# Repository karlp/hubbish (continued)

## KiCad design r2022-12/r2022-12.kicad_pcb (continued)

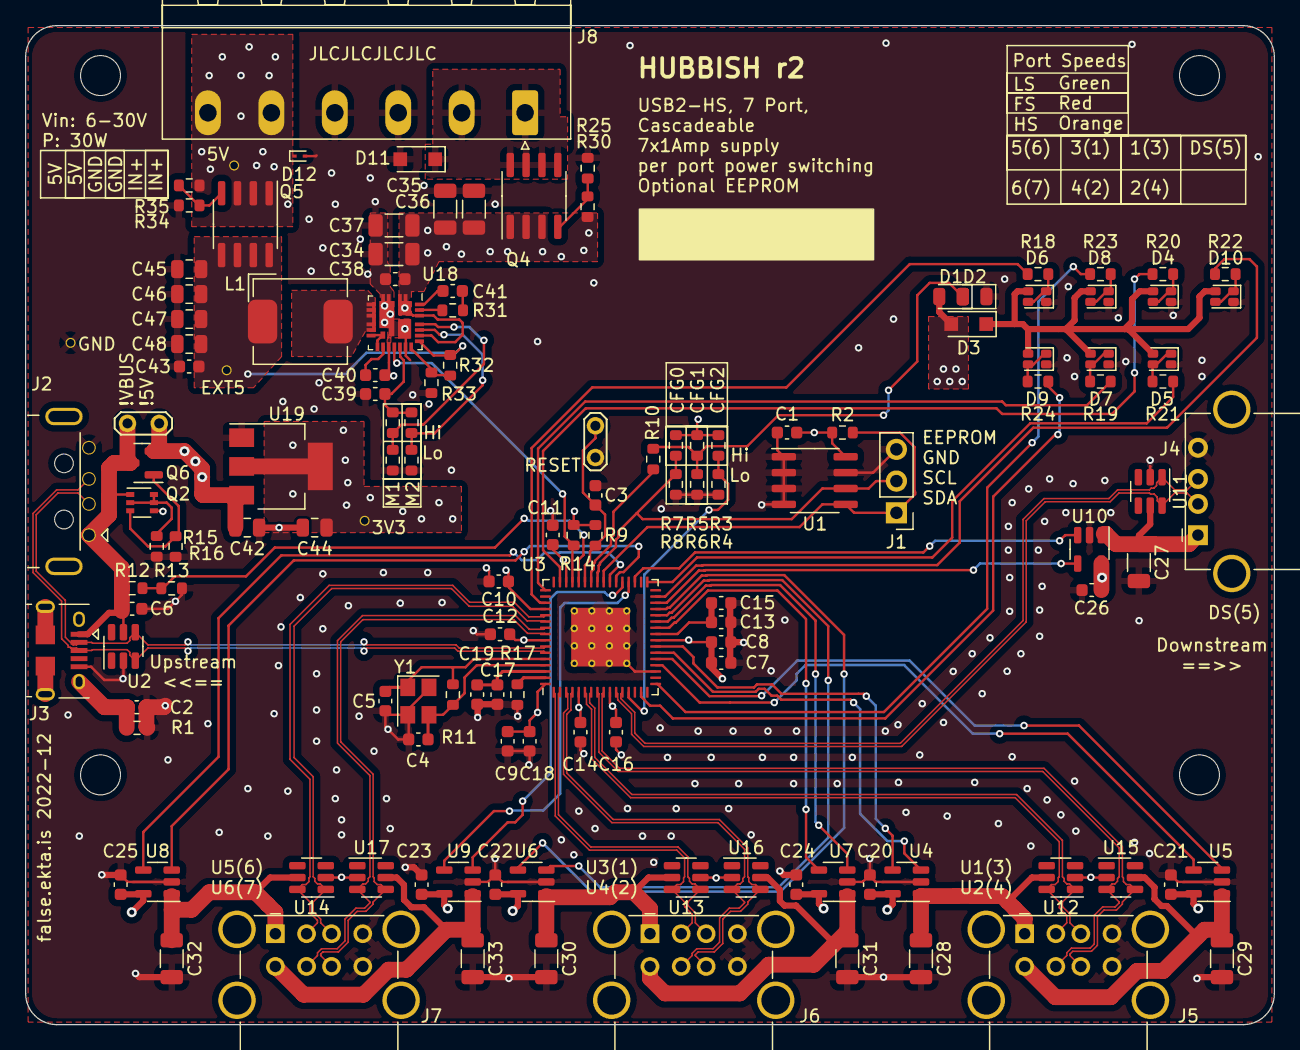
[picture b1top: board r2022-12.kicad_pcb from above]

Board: 4 copper layers, 100.0 x 80.0 mm, 138 parts (0 on the bottom side), 86 nets.

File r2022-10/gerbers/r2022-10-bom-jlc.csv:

"Comment","Designator","Footprint","JLCPCB Part #"
"100nF","C1,C2,C3,C8,C10,C11,C12,C14,C15,C16,C18,C19,C41,C44","Capacitor_SMD:C_0603_1608Metric","C14663"
"33pF","C4,C5","Capacitor_SMD:C_0603_1608Metric","C1663"
"1uF","C6,C7,C9,C13,C17,C20,C21,C22,C23,C24,C25,C26,C39,C40","Capacitor_SMD:C_0603_1608Metric","C15849"
"100uF","C27,C28,C29,C30,C31,C32,C33","Capacitor_SMD:C_1206_3216Metric","C15008"
"10uF/30+","C34,C35,C36,C37","Capacitor_SMD:C_1206_3216Metric","C13585 "
"100nF/30+","C38","Capacitor_SMD:C_0603_1608Metric","C14663"
"10uF","C42,C43,C45,C46,C47,C48","Capacitor_SMD:C_0805_2012Metric","C15850"
"HS1B","D1,D13","LED_SMD:LED_0805_2012Metric","C84256"
"HS1B","","LED_SMD:LED_0805_2012Metric","C84256"
"SM400x","D3","Diode_SMD:D_SOD-123F","C64898"
"LTST-C195KGJRKT","D4,D5,D6,D7,D8,D9,D10","LED_Dual:T1615_LiteOn_LTST_C195x","C125104"
"LTST-C195KGJRKT","","LED_Dual:T1615_LiteOn_LTST_C195x","C125104"
"LTST-C195KGJRKT","","LED_Dual:T1615_LiteOn_LTST_C195x","C125104"
"LTST-C195KGJRKT","","LED_Dual:T1615_LiteOn_LTST_C195x","C125104"
"LTST-C195KGJRKT","","LED_Dual:T1615_LiteOn_LTST_C195x","C125104"
"LTST-C195KGJRKT","","LED_Dual:T1615_LiteOn_LTST_C195x","C125104"
"USB_B_Micro (up)","J3","Connector_USB:USB_Micro-B_Amphenol_10118194-0001LF_Horizontal","C319164"
"USB_B_Micro (up)","","Connector_USB:USB_Micro-B_Amphenol_10118194-0001LF_Horizontal","C319164"
"USB_B_Micro (up)","","Connector_USB:USB_Micro-B_Amphenol_10118194-0001LF_Horizontal","C319164"
"USB_B_Micro (up)","","Connector_USB:USB_Micro-B_Amphenol_10118194-0001LF_Horizontal","C319164"
"USB_B_Micro (up)","","Connector_USB:USB_Micro-B_Amphenol_10118194-0001LF_Horizontal","C319164"
"1.5uH","L1","Inductor_SMD:L_Chilisin_BMRx00060630","C329386"
"HSM6115","Q1","Package_SO:SOIC-8_3.9x4.9mm_P1.27mm","C700986"
"S8550","Q2,Q4","Package_TO_SOT_SMD:SOT-23","C105432"
"AO3401A","Q3","Package_TO_SOT_SMD:SOT-23","C15127"
"330","R1,R10,R18,R19,R20,R21,R22,R30,R32,R33","Resistor_SMD:R_0603_1608Metric","C23138"
"10k","R2,R4,R5,R7,R11,R15,R16,R23,R34","Resistor_SMD:R_0603_1608Metric","C25804"
"100k","R9,R13,R14,R26","Resistor_SMD:R_0603_1608Metric","C25803"
"1M","R12","Resistor_SMD:R_0603_1608Metric","C22935"
"12k","R17","Resistor_SMD:R_0603_1608Metric","C22790"
"20k","R24","Resistor_SMD:R_0603_1608Metric","C4184"
"20k","","Resistor_SMD:R_0603_1608Metric","C4184"
"510k","R28","Resistor_SMD:R_0603_1608Metric","C23192"
"0","R29","Resistor_SMD:R_0603_1608Metric","C21189"
"75k","R31","Resistor_SMD:R_0603_1608Metric","C23242"
"75k","","Resistor_SMD:R_0603_1608Metric","C23242"
"2k i2c eeprom","U1","Package_SO:SOIC-8_3.9x4.9mm_P1.27mm","C7562"
"NUP4202","U2,U11,U12,U13,U14,U15,U16,U17","Package_TO_SOT_SMD:SOT-23-6","C85364"
"USB2517","U3","Package_DFN_QFN:QFN-64-1EP_9x9mm_P0.5mm_EP4.7x4.7mm_ThermalVias","C626667"
"APL3511C","U4,U5,U6,U7,U8,U9,U10","Package_TO_SOT_SMD:SOT-23-5","C211404"
"SiC437AED","U18","Package_DFN_QFN:Vishay_MLP-44L_4x4","C2071432"
"AMS1117-33","U19","Package_TO_SOT_SMD:SOT-223-3_TabPin2","C6186"
"24MHz","Y1","Crystal:Crystal_SMD_3225-4Pin_3.2x2.5mm","C70590"

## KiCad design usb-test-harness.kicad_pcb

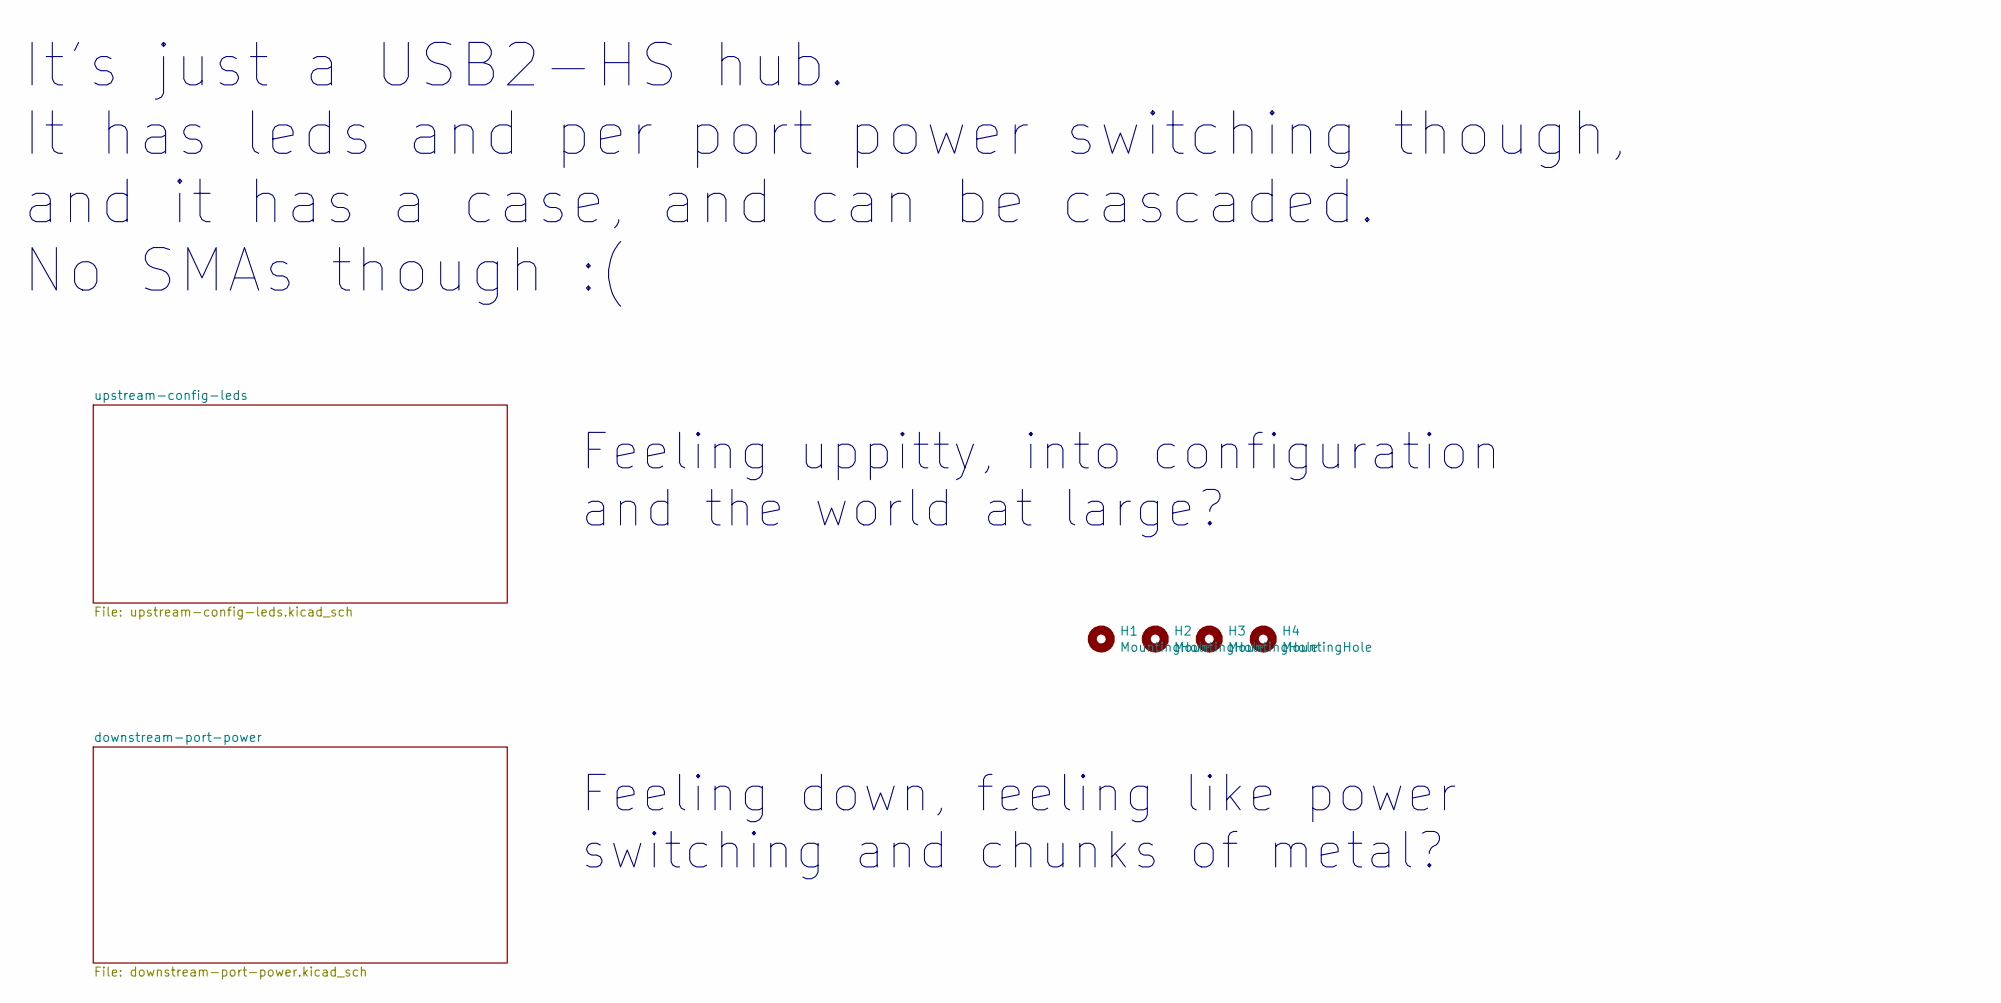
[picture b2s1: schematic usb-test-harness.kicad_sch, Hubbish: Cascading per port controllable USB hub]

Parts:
H1, H2, H3, H4: MountingHole; MountingHole_2.7mm_M2.5

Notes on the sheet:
It's just a USB2-HS hub. It has leds and per port power switching though, and it has a case, and can be cascaded. No SMAs though :(
Feeling uppitty, into configuration and the world at large?
Feeling down, feeling like power switching and chunks of metal?

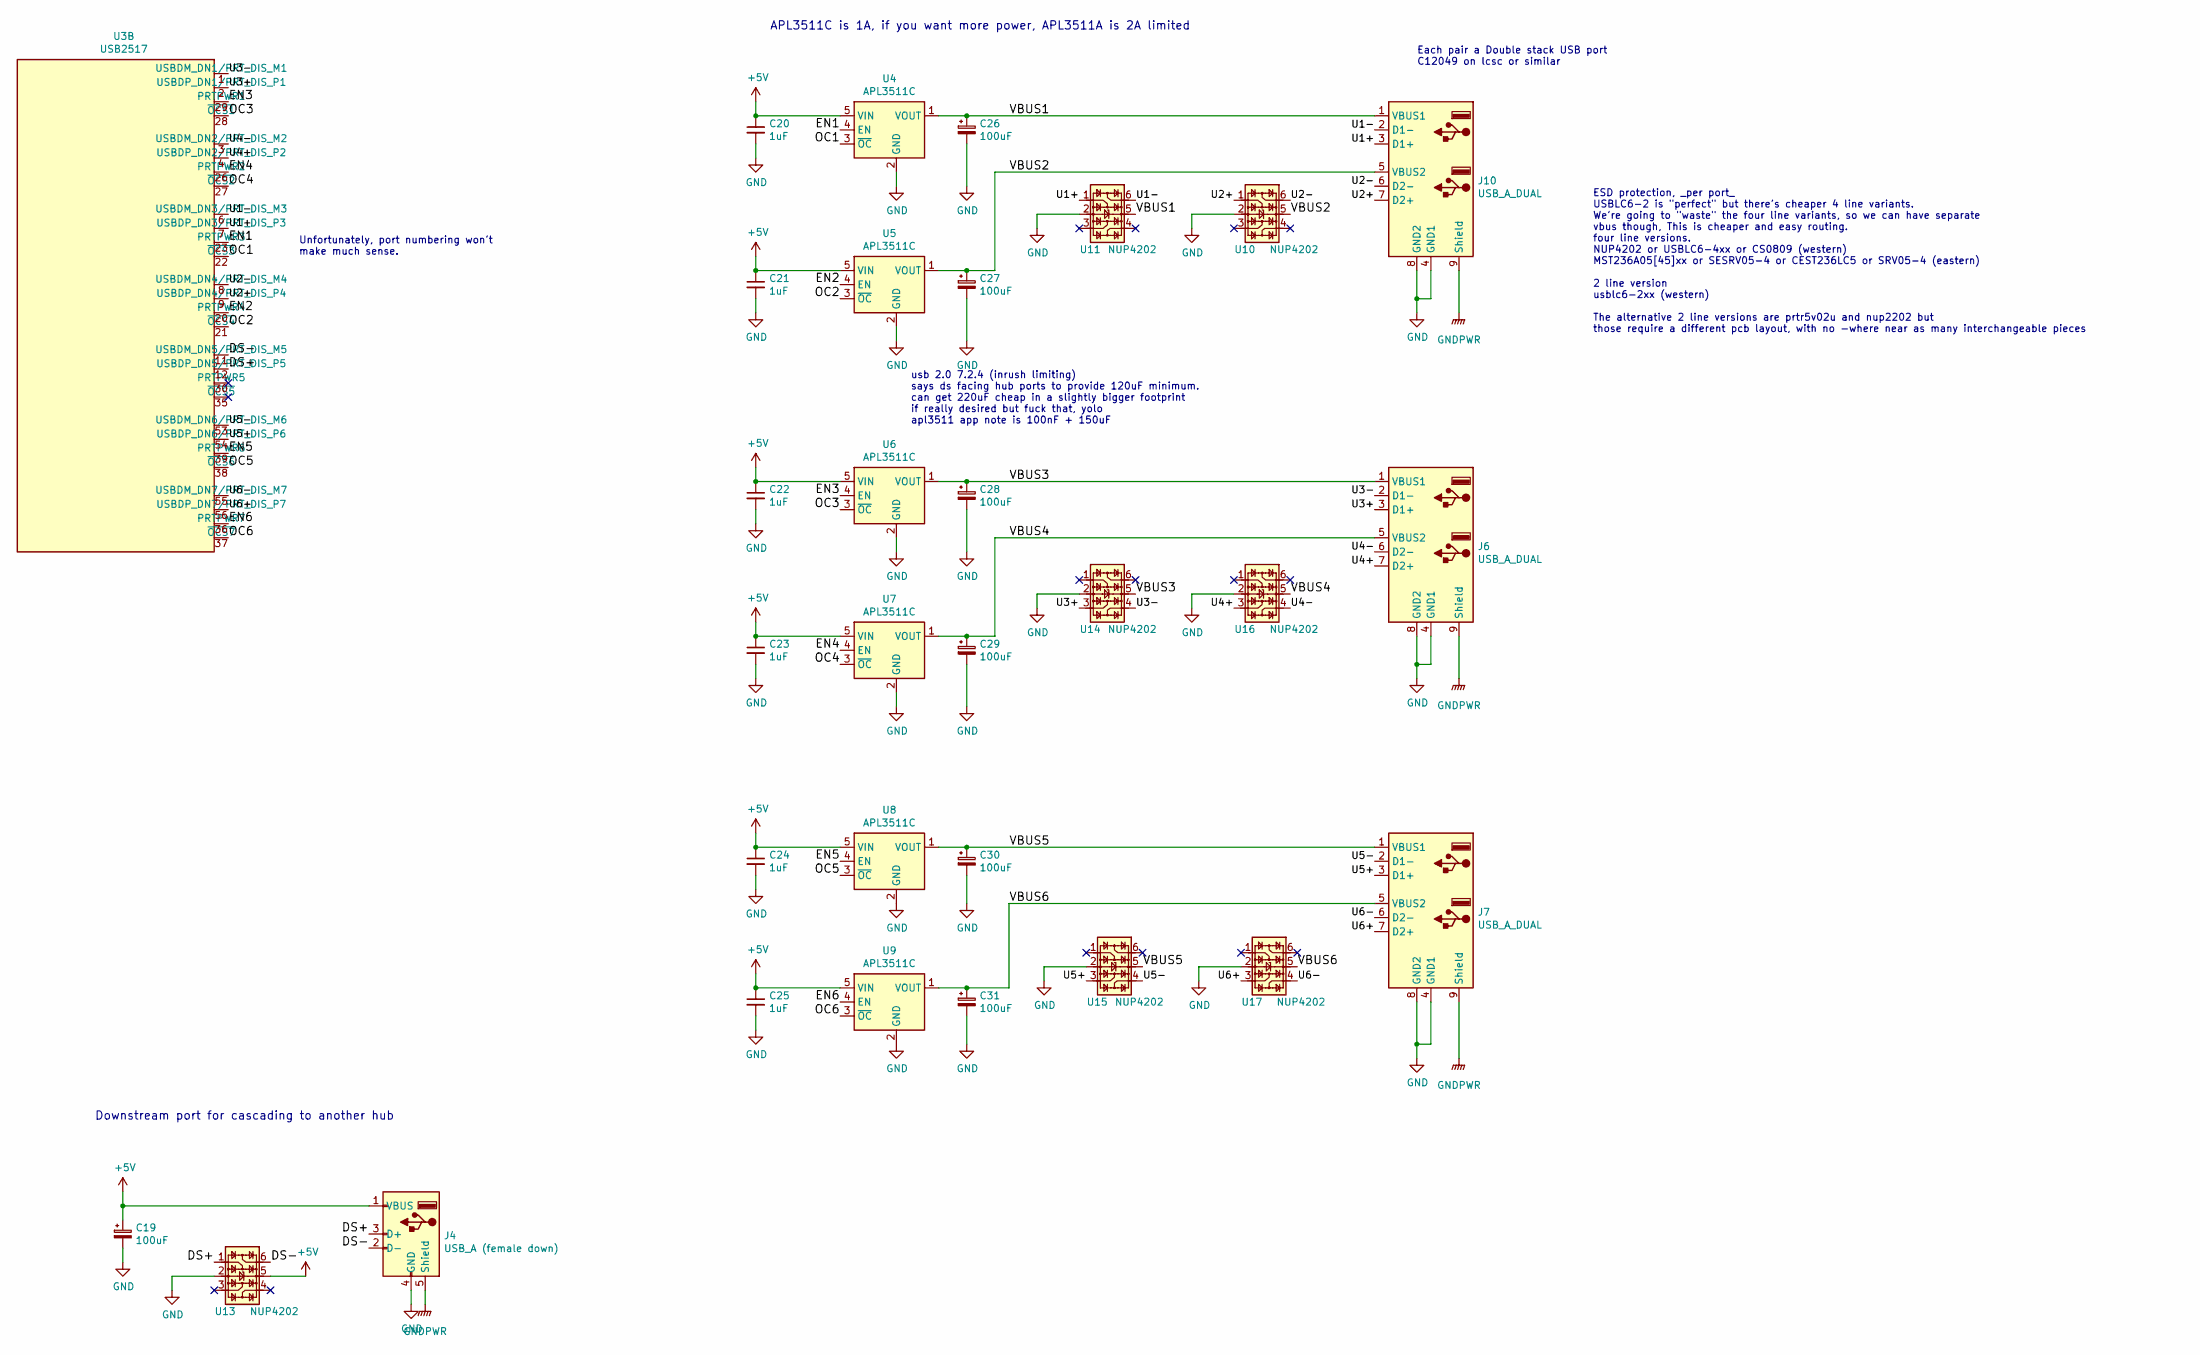
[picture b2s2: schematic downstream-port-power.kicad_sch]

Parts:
C19, C26, C27, C28, C29, C30, C31: 100uF; CP_Elec_5x5.4
C20, C21, C22, C23, C24, C25: 1uF; C_0603_1608Metric
J4: USB_A (female down); USB_A_Stewart_SS-52100-001_Horizontal; MPN C42643 or SS-52100 compatible
J6, J7, J10: USB_A_DUAL; USB_A_Wuerth_61400826021_Horizontal_Stacked
U3: USB2517; QFN-64-1EP_9x9mm_P0.5mm_EP4.7x4.7mm_ThermalVias
U4, U5, U6, U7, U8, U9: APL3511C; SOT-23-5
U10, U11, U13, U14, U15, U16, U17: NUP4202; SOT-23-6

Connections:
+5V: C19.1, C20.1, C21.1, C22.1, C23.1, C24.1, C25.1, J4.1 (VBUS), U4.5 (VIN), U5.5 (VIN), U6.5 (VIN), U7.5 (VIN), U8.5 (VIN), U9.5 (VIN), U13.5; also elsewhere on the board
/downstream-port-power/DS+: J4.3 (D+), U3.12 (USBDP_DN5/PRT_DIS_P5), U13.1
/downstream-port-power/DS-: J4.2 (D-), U3.11 (USBDM_DN5/PRT_DIS_M5), U13.6
/downstream-port-power/EN1: U3.23 (PRTPWR3), U4.4 (EN)
/downstream-port-power/EN2: U3.20 (PRTPWR4), U5.4 (EN)
/downstream-port-power/EN3: U3.29 (PRTPWR1), U6.4 (EN)
/downstream-port-power/EN4: U3.26 (PRTPWR2), U7.4 (EN)
/downstream-port-power/EN5: U3.39 (PRTPWR6), U8.4 (EN)
/downstream-port-power/EN6: U3.36 (PRTPWR7), U9.4 (EN)
/downstream-port-power/OC1: U3.22 (~OCS3), U4.3 (~OC)
/downstream-port-power/OC2: U3.21 (~OCS4), U5.3 (~OC)
/downstream-port-power/OC3: U3.28 (~OCS1), U6.3 (~OC)
/downstream-port-power/OC4: U3.27 (~OCS2), U7.3 (~OC)
/downstream-port-power/OC5: U3.38 (~OCS6), U8.3 (~OC)
/downstream-port-power/OC6: U3.37 (~OCS7), U9.3 (~OC)
/downstream-port-power/U1+: J10.3 (D1+), U3.7 (USBDP_DN3/PRT_DIS_P3), U11.1
/downstream-port-power/U1-: J10.2 (D1-), U3.6 (USBDM_DN3/PRT_DIS_M3), U11.6
/downstream-port-power/U2+: J10.7 (D2+), U3.9 (USBDP_DN4/PRT_DIS_P4), U10.1
/downstream-port-power/U2-: J10.6 (D2-), U3.8 (USBDM_DN4/PRT_DIS_M4), U10.6
/downstream-port-power/U3+: J6.3 (D1+), U3.2 (USBDP_DN1/PRT_DIS_P1), U14.3
/downstream-port-power/U3-: J6.2 (D1-), U3.1 (USBDM_DN1/PRT_DIS_M1), U14.4
/downstream-port-power/U4+: J6.7 (D2+), U3.4 (USBDP_DN2/PRT_DIS_P2), U16.3
/downstream-port-power/U4-: J6.6 (D2-), U3.3 (USBDM_DN2/PRT_DIS_M2), U16.4
/downstream-port-power/U5+: J7.3 (D1+), U3.54 (USBDP_DN6/PRT_DIS_P6), U15.3
/downstream-port-power/U5-: J7.2 (D1-), U3.53 (USBDM_DN6/PRT_DIS_M6), U15.4
/downstream-port-power/U6+: J7.7 (D2+), U3.56 (USBDP_DN7/PRT_DIS_P7), U17.3
/downstream-port-power/U6-: J7.6 (D2-), U3.55 (USBDM_DN7/PRT_DIS_M7), U17.4
/downstream-port-power/VBUS1: C26.1, J10.1 (VBUS1), U4.1 (VOUT), U11.5
/downstream-port-power/VBUS2: C27.1, J10.5 (VBUS2), U5.1 (VOUT), U10.5
/downstream-port-power/VBUS3: C28.1, J6.1 (VBUS1), U6.1 (VOUT), U14.5
/downstream-port-power/VBUS4: C29.1, J6.5 (VBUS2), U7.1 (VOUT), U16.5
/downstream-port-power/VBUS5: C30.1, J7.1 (VBUS1), U8.1 (VOUT), U15.5
/downstream-port-power/VBUS6: C31.1, J7.5 (VBUS2), U9.1 (VOUT), U17.5
GND: C19.2, C20.2, C21.2, C22.2, C23.2, C24.2, C25.2, C26.2, C27.2, C28.2, C29.2, C30.2, C31.2, J4.4 (GND), J6.4 (GND1), J6.8 (GND2), J7.4 (GND1), J7.8 (GND2), J10.4 (GND1), J10.8 (GND2), U4.2 (GND), U5.2 (GND), U6.2 (GND), U7.2 (GND), U8.2 (GND), U9.2 (GND), U10.2, U11.2, U13.2, U14.2, U15.2, U16.2, U17.2; also elsewhere on the board
GNDPWR: J4.5 (Shield), J6.9 (Shield), J7.9 (Shield), J10.9 (Shield); also elsewhere on the board

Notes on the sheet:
Downstream port for cascading to another hub
Unfortunately, port numbering won't make much sense.
APL3511C is 1A, if you want more power, APL3511A is 2A limited
usb 2.0 7.2.4 (inrush limiting) says ds facing hub ports to provide 120uF minimum. can get 220uF cheap in a slightly bigger footprint if really desired but fuck that, yolo apl3511 app note is 100nF + 150uF
Each pair a Double stack USB port C12049 on lcsc or similar
ESD protection, _per port_ USBLC6-2 is "perfect" but there's cheaper 4 line variants. We're going to "waste" the four line variants, so we can have separate vbus though, This is cheaper and easy routing. four line versions. NUP4202 or USBLC6-4xx or CS0809 (western) MST236A05[45]xx or SESRV05-4 or C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

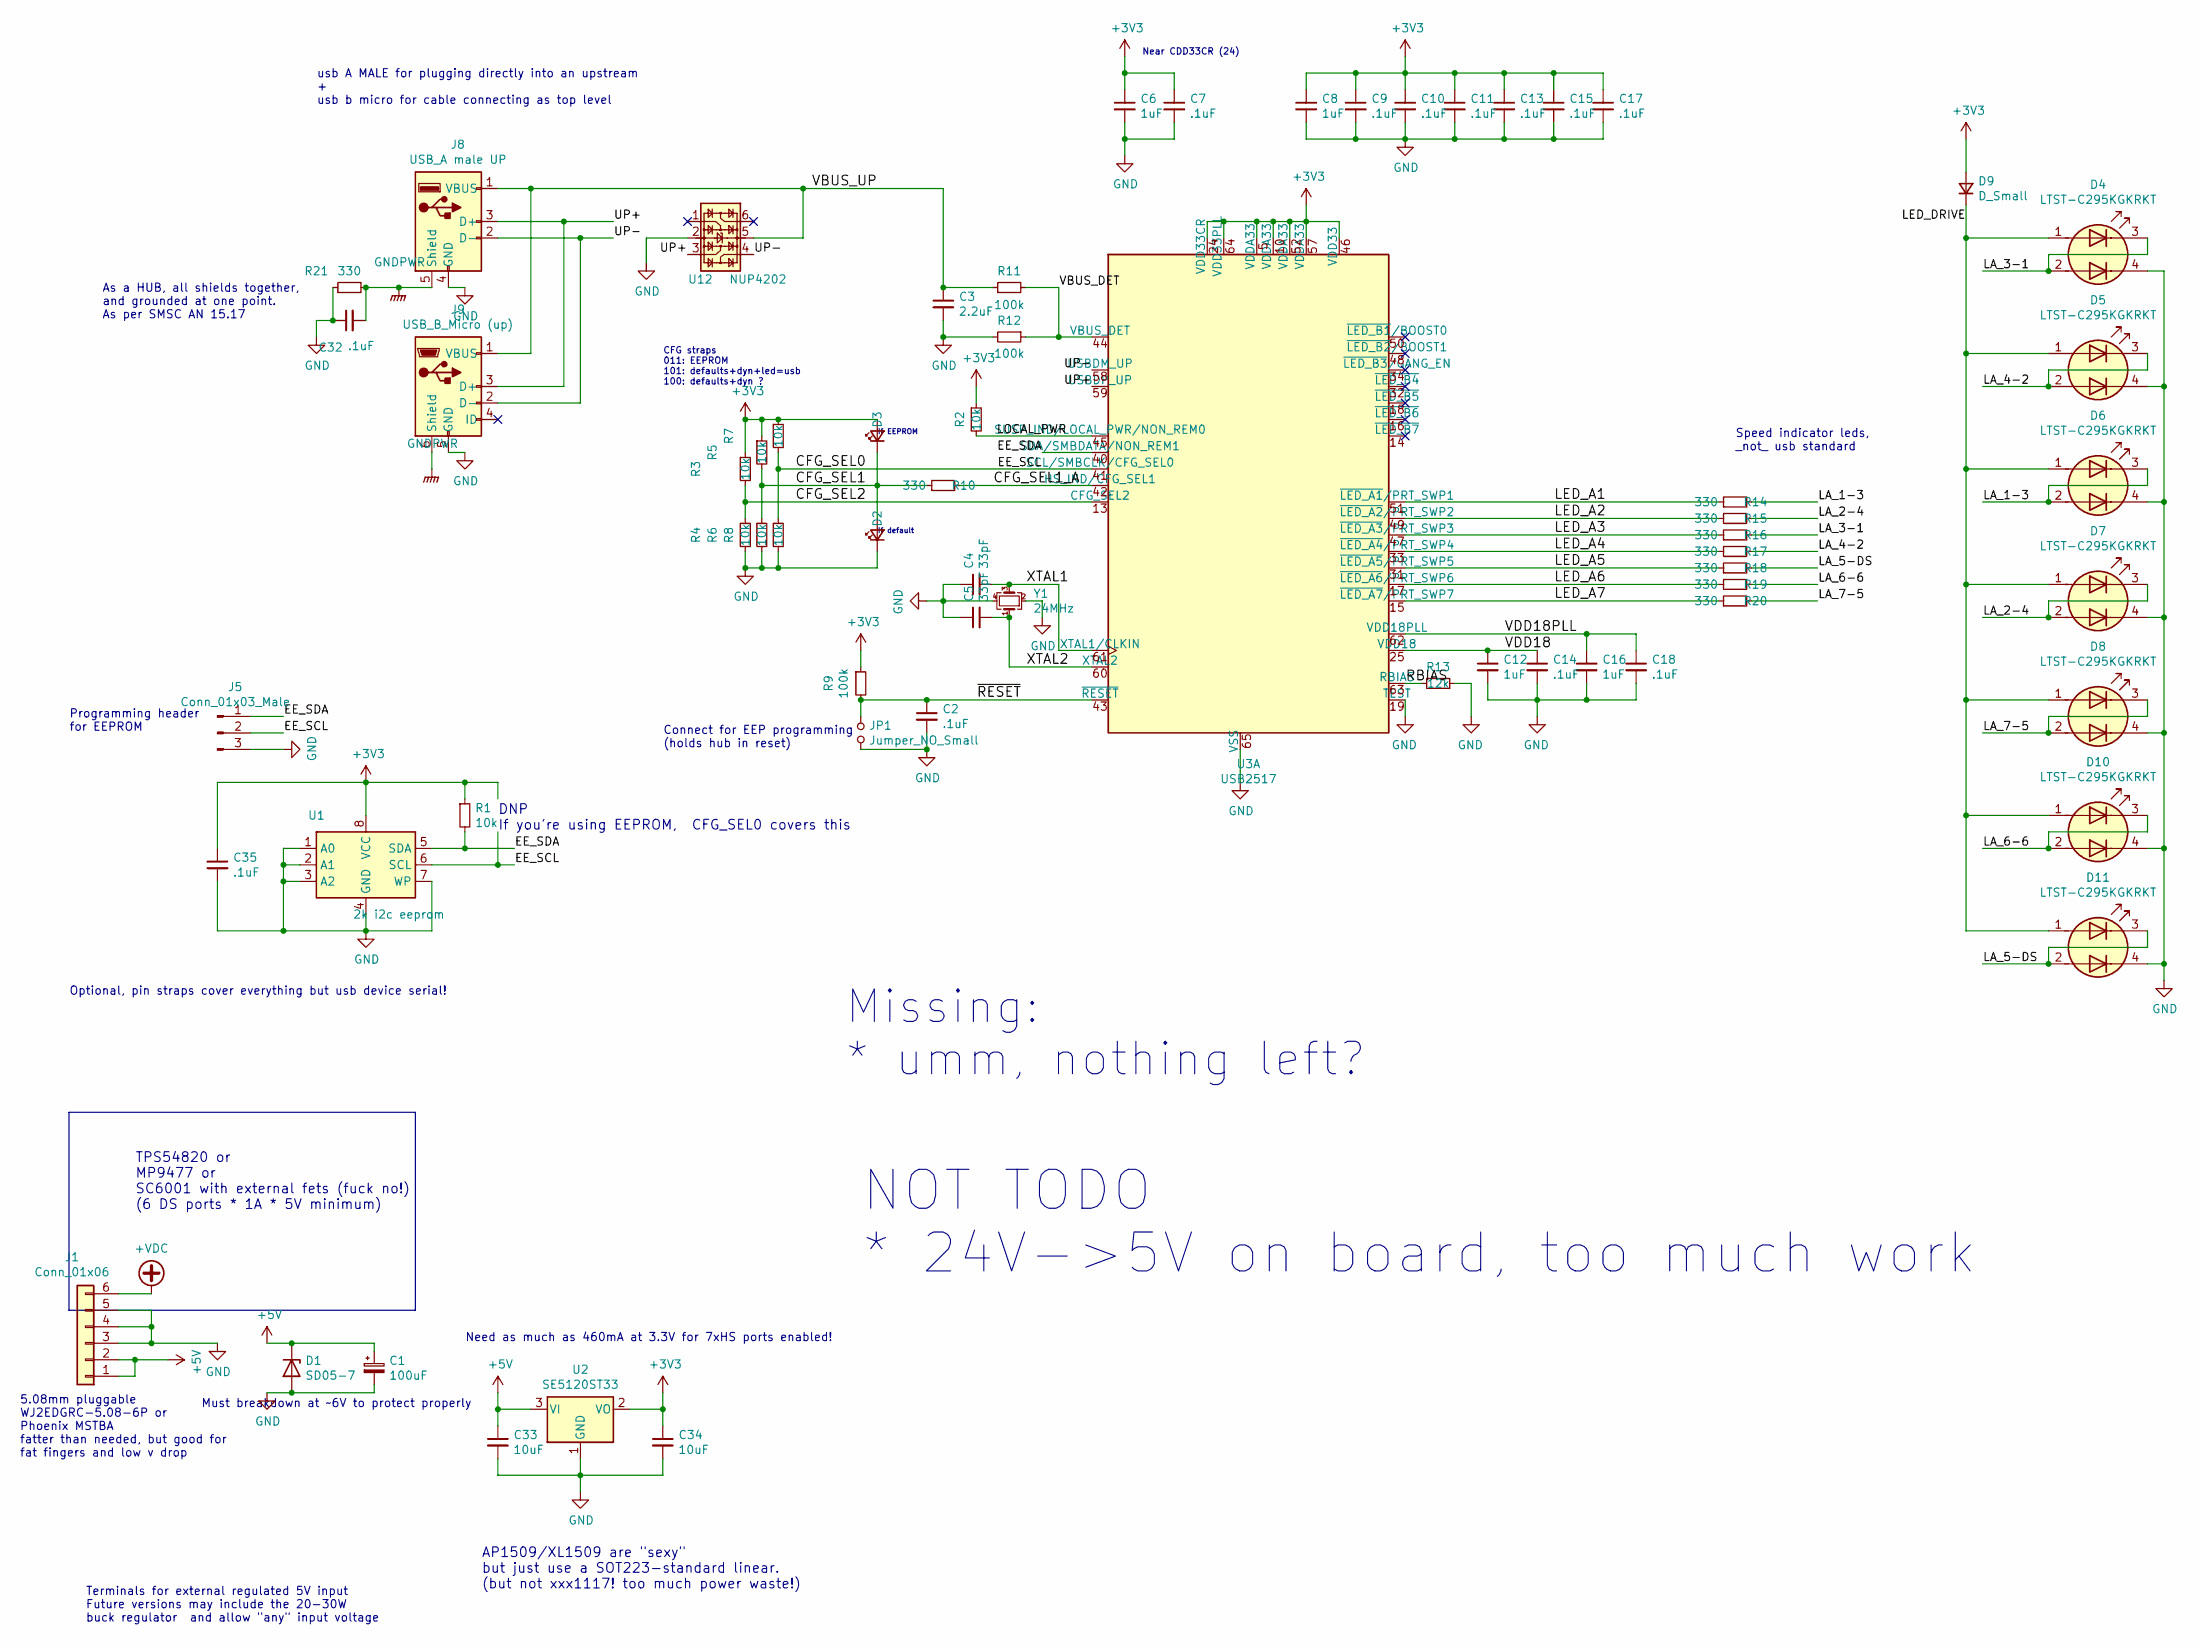
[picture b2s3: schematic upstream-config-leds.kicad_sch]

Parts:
C1: 100uF; CP_Elec_5x5.4
C2, C7, C9, C10, C11, C13, C14, C15, C17, C18, C32, C35: .1uF; C_0603_1608Metric
C3: 2.2uF; C_0603_1608Metric
C4, C5: 33pF; C_0603_1608Metric
C6, C8, C12, C16: 1uF; C_0603_1608Metric
C33, C34: 10uF; C_0603_1608Metric
D1: SD05-7; D_SOD-323
D2: HS1A; LED_0603_1608Metric
D3: HS1B; LED_0603_1608Metric
D4, D5, D6, D7, D8, D10, D11: LTST-C295KGKRKT; LED_LiteOn_LTST-C295K
D9: D_Small; D_SOD-323
J1: Conn_01x06; PhoenixContact_MSTBA_2,5_6-G-5,08_1x06_P5.08mm_Horizontal
J5: Conn_01x03_Male; PinHeader_1x03_P2.54mm_Vertical
J8: USB_A male UP; USB_A_Plug_SOFNG_USB-05; MPN SOFNG USB-05
J9: USB_B_Micro (up); USB_Micro-B_Amphenol_10118194-0001LF_Horizontal; MPN U254-051T-4BH23-S2B
JP1: Jumper_NO_Small; PinHeader_1x02_P2.54mm_Vertical
R1, R2, R3, R4, R5, R6, R7, R8: 10k; R_0603_1608Metric
R9, R11, R12: 100k; R_0603_1608Metric
R10, R14, R15, R16, R17, R18, R19, R20, R21: 330; R_0603_1608Metric
R13: 12k; R_0603_1608Metric
U1: 2k i2c eeprom; SOIC-8_3.9x4.9mm_P1.27mm; MPN FT24C02A
U2: SE5120ST33; SOT-223-3_TabPin2; MPN SE5120ST33
U3: USB2517; QFN-64-1EP_9x9mm_P0.5mm_EP4.7x4.7mm_ThermalVias
U12: NUP4202; SOT-363_SC-70-6
Y1: 24MHz; Crystal_SMD_3225-4Pin_3.2x2.5mm

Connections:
+3V3: C6.1, C7.1, C8.1, C9.1, C10.1, C11.1, C13.1, C15.1, C17.1, C34.1, C35.1, D3.2 (A), D9.2 (A), R1.1, R2.1, R3.1, R5.1, R7.1, R9.1, U1.8 (VCC), U2.2 (VO), U3.5 (VDDA33), U3.10 (VDDA33), U3.24 (VDD33CR), U3.46 (VDD33), U3.52 (VDDA33), U3.57 (VDDA33), U3.64 (VDD33PLL)
+5V: C1.1, C33.1, D1.1 (K), J1.1, J1.2, U2.3 (VI); also elsewhere on the board
/upstream-config-leds/CFG_SEL0: J5.2, R7.2, R8.1, U1.6 (SCL), U3.41 (SCL/SMBCLK/CFG_SEL0)
/upstream-config-leds/CFG_SEL1: D2.2 (A), D3.1 (K), R5.2, R6.1, R10.1
/upstream-config-leds/CFG_SEL1_A: R10.2, U3.42 (HS_IND/CFG_SEL1)
/upstream-config-leds/CFG_SEL2: R3.2, R4.1, U3.13 (CFG_SEL2)
/upstream-config-leds/EE_SDA: J5.1, R1.2, U1.5 (SDA), U3.40 (SDA/SMBDATA/NON_REM1)
/upstream-config-leds/LA_1-3: D6.2 (A2), D6.3 (K1), R14.2
/upstream-config-leds/LA_2-4: D7.2 (A2), D7.3 (K1), R15.2
/upstream-config-leds/LA_3-1: D4.2 (A2), D4.3 (K1), R16.2
/upstream-config-leds/LA_4-2: D5.2 (A2), D5.3 (K1), R17.2
/upstream-config-leds/LA_5-DS: D11.2 (A2), D11.3 (K1), R18.2
/upstream-config-leds/LA_6-6: D10.2 (A2), D10.3 (K1), R19.2
/upstream-config-leds/LA_7-5: D8.2 (A2), D8.3 (K1), R20.2
/upstream-config-leds/LED_A1: R14.1, U3.51 (~LED_A1~/PRT_SWP1)
/upstream-config-leds/LED_A2: R15.1, U3.49 (~LED_A2~/PRT_SWP2)
/upstream-config-leds/LED_A3: R16.1, U3.47 (~LED_A3~/PRT_SWP3)
/upstream-config-leds/LED_A4: R17.1, U3.33 (~LED_A4~/PRT_SWP4)
/upstream-config-leds/LED_A5: R18.1, U3.31 (~LED_A5~/PRT_SWP5)
/upstream-config-leds/LED_A6: R19.1, U3.17 (~LED_A6~/PRT_SWP6)
/upstream-config-leds/LED_A7: R20.1, U3.15 (~LED_A7~/PRT_SWP7)
/upstream-config-leds/LED_DRIVE: D4.1 (A1), D5.1 (A1), D6.1 (A1), D7.1 (A1), D8.1 (A1), D9.1 (K), D10.1 (A1), D11.1 (A1)
/upstream-config-leds/LOCAL_PWR: R2.2, U3.45 (SUSP_IND/LOCAL_PWR/NON_REM0)
/upstream-config-leds/RBIAS: R13.1, U3.63 (RBIAS)
/upstream-config-leds/UP+: J8.3 (D+), J9.3 (D+), U3.59 (USBDP_UP), U12.3
/upstream-config-leds/UP-: J8.2 (D-), J9.2 (D-), U3.58 (USBDM_UP), U12.4
/upstream-config-leds/VBUS_DET: R11.2, R12.1, U3.44 (VBUS_DET)
/upstream-config-leds/VBUS_UP: C3.1, J8.1 (VBUS), J9.1 (VBUS), R11.1, U12.5
/upstream-config-leds/VDD18: C12.1, C14.1, U3.25 (VDD18)
/upstream-config-leds/VDD18PLL: C16.1, C18.1, U3.62 (VDD18PLL)
/upstream-config-leds/XTAL1: C4.2, U3.61 (XTAL1/CLKIN), Y1.3
/upstream-config-leds/XTAL2: C5.2, U3.60 (XTAL2), Y1.1
/upstream-config-leds/~RESET: C2.1, JP1.1, R9.2, U3.43 (~RESET)
GND: C1.2, C2.2, C3.2, C4.1, C5.1, C6.2, C7.2, C8.2, C9.2, C10.2, C11.2, C12.2, C13.2, C14.2, C15.2, C16.2, C17.2, C18.2, C32.1, C33.2, C34.2, C35.2, D1.2 (A), D2.1 (K), D4.4 (K2), D5.4 (K2), D6.4 (K2), D7.4 (K2), D8.4 (K2), D10.4 (K2), D11.4 (K2), J1.3, J1.4, J1.5, J5.3, J8.4 (GND), J9.5 (GND), JP1.2, R4.2, R6.2, R8.2, R12.2, R13.2, R21.1, U1.1 (A0), U1.2 (A1), U1.3 (A2), U1.4 (GND), U1.7 (WP), U2.1 (GND), U3.19 (TEST), U3.65 (VSS), U12.2, Y1.2, Y1.4; also elsewhere on the board
GNDPWR: C32.2, J8.5 (Shield), J9.6 (Shield), R21.2; also elsewhere on the board

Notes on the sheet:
5.08mm pluggable WJ2EDGRC-5.08-6P or Phoenix MSTBA fatter than needed, but good for fat fingers and low v drop
Programming header for EEPROM
Optional, pin straps cover everything but usb device serial!
Terminals for external regulated 5V input Future versions may include the 20-30W buck regulator and allow "any" input voltage
As a HUB, all shields together, and grounded at one point. As per SMSC AN 15.17
TPS54820 or MP9477 or SC6001 with external fets (fuck no!) (6 DS ports * 1A * 5V minimum)
Must breakdown at ~~6V to protect properly
usb A MALE for plugging directly into an upstream + usb b micro for cable connecting as top level
Need as much as 460mA at 3.3V for 7xHS ports enabled!
AP1509/XL1509 are "sexy" but just use a SOT223-standard linear. (but not xxx1117! too much power waste!)
DNP If you're using EEPROM, CFG_SEL0 covers this
CFG straps 011: EEPROM 101: defaults+dyn+led=usb 100: defaults+dyn ?
Connect for EEP programming (holds hub in reset)
Missing: * umm, nothing left?
NOT TODO * 24V->5V on board, too much work
If EEPROM
If default
Near CDD33CR (24)
Speed indicator leds, _not_ usb standard

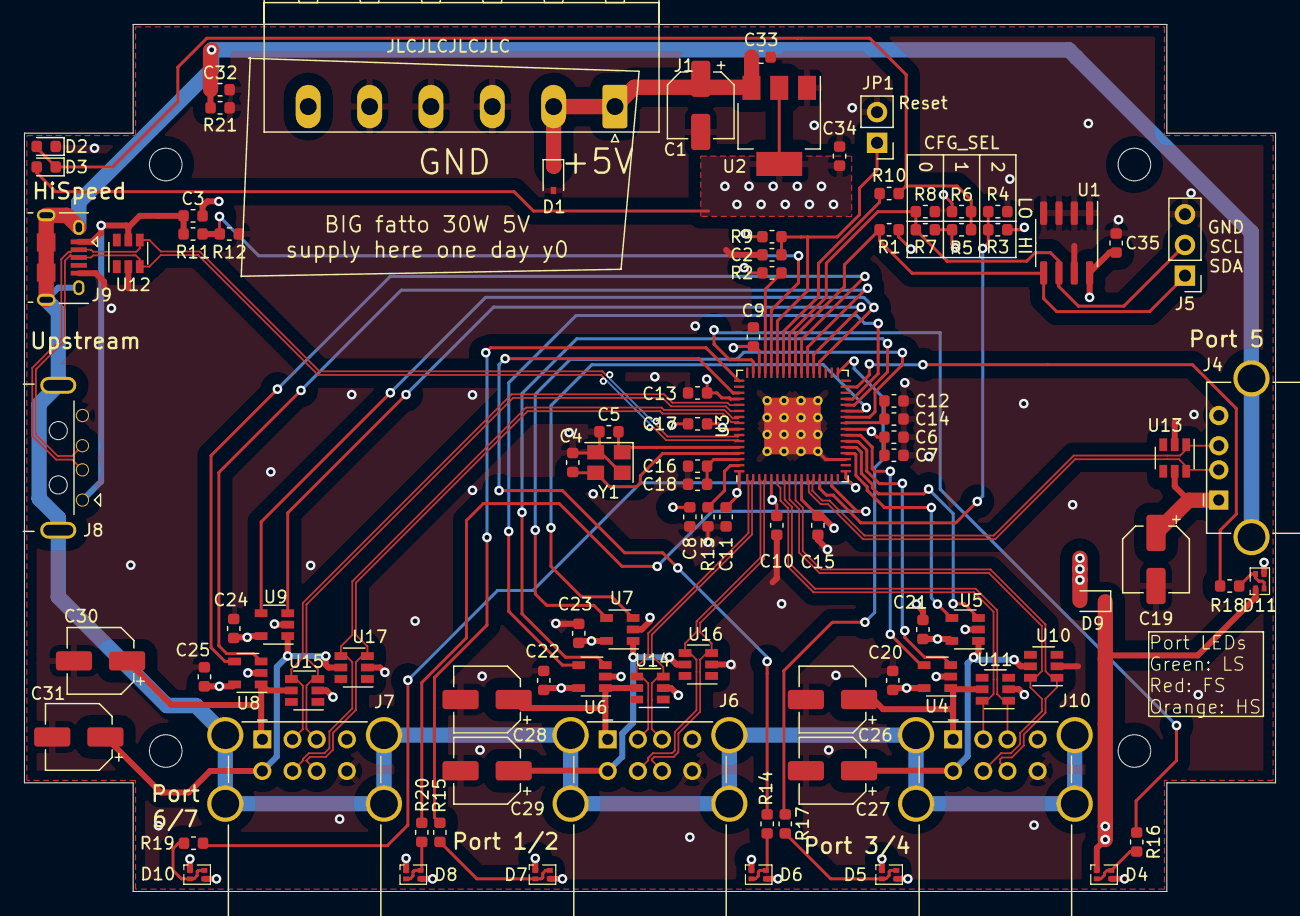
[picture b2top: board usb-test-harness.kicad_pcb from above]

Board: 4 copper layers, 103.6 x 71.8 mm, 98 parts (0 on the bottom side), 67 nets.

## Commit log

2019-12-03 insane ideas on our own usb hub board
    stackable sideways to make it easier to lay out
    chainable power terminals
    dual "DUT" usb ports for discovery/etc boards with an stlink and a user
    usb port.
2019-12-03 hw: usb-test-harness: more hacking on a hub
    this is insane.
2019-12-03 hw: usb test harness: add docs
2019-12-03 running pdf for madness
2020-01-10 usb-test-harness: save point before refactor
    We moved to usb2517 to keep config simple, but we're about to gut the
    symbol and break the schematic apart even further.
2020-01-11 usb-test-harness: split hub symbol
    all night long, and we split a symbol. yay
2020-01-11 hw: usb-test-harness: split, heirarchical
2020-01-11 usb-test-harness: getting there...
2020-02-28 usb-test-harness: updated usb footprints, working on it again
    Just trying to finalise the connectors before getting down to brass
    tacks
2020-03-07 usb hub: choose a box, redraw frame
    Closer and closer
    Now we have an enclosure: https://www.tme.eu/is/en/details/abs-35/enclosures-with-panel/maszczyk/km-35-gy/
    Set up the holes and outline properly. Now we can really get started.
2020-03-08 hub: we've chosen leds poorly.
    We can't _really_ get away with using two discrete leds to try and get a
    bicolour effect, it's just going to be weird.
    A side mount bi colour independent woudl be good, but cant' find one
    cheaply, and top mount will be fine I think....
2020-03-08 usb-hub: update leds and add footprint for it
2020-03-10 usb-hub: pickd SOD-123F as footprint for diodes
    SMA is very common, but bigger, SOD-123F is just as cheap, and more than
    suitable.
2020-03-10 usb-hub: pcb: precisely layout all the connectors again
    lock them in place, properly even and nice and clean now. Now you can
    _really_ start routing.
2020-03-11 usb-hub: switch to newer amphenol micro b
    this makes it feasible to route usb properly. Then, charge ahead with
    routing. Started with the 3v3 and hub power parts, now continuing with
    the enable/overcurrent parts. leds will be last.
2020-03-11 usb-hub: finish all enable/oc lines, fix warnings
    just leds, led drive, usb shields, and the big 5v mainline left.
2020-03-11 usb-hub: fix broken diff pair after push n shove
2020-03-11 usb-hub: fix more diff pairs broken by moving things.
2020-03-13 usb-hub: just shields and silk left.
    finished all the leds and controls
2020-03-13 usb-hub: add local power connection
    Somehow felt that "dynamic power" was going to magically save things
    here. It does not! required a bit of re-routing.
2020-03-13 usb-hub: expand spacing on top ground
    cypress design guide, try not to have same plane ground too close to
    d+/d- traces
2020-03-14 usb-hub: decide shields per app note
    SMSC 15.17 guidelines for usb hubs seem sensible and relevant.
    Connect all the shields together, and to ground at one point.
2020-03-14 usb-hub: tidy up lots of silk
2020-03-20 usb-hub: sch notes on todo, esd protection and inrush
    pcb only had silk pushing i think. kicad nightlies are trashing diffs
    :|
2020-03-20 give hubbish it's own readme.
2020-03-20 add current pdf of sch
2020-03-23 updates: bits
    * add in/out caps on 3v3 supply (how was that missed?)
    * switch to pluggable terminal blocks. better forr case design, better
    for humans, ~same price
    * added more notes on suitable esd protection on usb
    * still no input protection on 5v.
    * Added the stupid mounting hole that ruins it all with the current
2020-03-25 last update before changing box design
    original box is lovely, and cheap, but only available on TME, so we've
    found a new box, Bud CU-388, available on dk and mouser as well, at a
    nearly as good price.
2020-03-25 enclosures: add Bud CU-388 docs
    step file was emailed on request from bud, no license attached. dxf and
    pdf are from their website.
2020-04-12 Updated "finished" for new bud cu-388 box
2020-04-25 Added esd protection.
    Still haven't re-routed the upstream side yet, but nearly.
2020-04-27 "finished" upstream ESD, silk, text and commentary
    Nearly there?
2020-04-27 add latest plot pdf
2020-04-28 more silk and polish tweaks
2020-06-24 pcb: expand usb hub vias to 0.4mm for cheaper manufacturing
    also, added jlc text for pcb order number
2020-09-28 accept project changes to old file
2020-09-28 Add new project version files
2020-09-28 Add TODO
2020-09-28 update pcb to latest proj version too
2021-02-08 gitignore lots of dangling bits
2021-02-08 add production gerbers from rev1
2021-02-08 move parts docs into one tree
2021-02-08 add all datasheets for project as is
2021-02-08 update project file formats again?
    not sure anything _changed_
2021-02-08 my hacked up guideline for pcb for the bud case
2021-02-08 freecad model of fit
    step file from kicad export, plus bud case model
2021-02-08 note that we're using kicad 5.99+
2021-02-08 touch some text and resave to get all latest file formats
2021-02-08 prepare for a new revision
2021-02-09 initial work on new revision
2021-02-17 switch to upstream dual usb symbol
    less private local parts, more better.
2021-02-28 start rev2
2021-03-01 r2: use a fet for polarity protection
    don't be dumb and use a schottkey, you're doing a 30W supply!
2021-03-10 sch: rev2: update to latest kicad, add power flags.
    cleared all ERC errors/warnings
2021-03-11 rev2: start pcb work.
    Looks like lots of space on a 100mm square...
2021-12-07 hubbish 2021-2 updates
    line it up a bit better, realise parts are no longer available, start
    kidding myself I'm working on this again.
2021-12-10 r2021-02: "finish" routing
    it's kinda untidy, but it's all routed out now, except for where I need
    to replace the power supply
2021-12-28 hw-rev2: break out power input to a new sheet
    It was always a bit crowded there, and now that we need to pick new
    parts, we want a little more space...
2021-12-30 hw: r2: clarify parts and values for polarity protection
    falstad simulation:
    $ 1 0.000005 10.20027730826997 50 5 50 5e-11
    34 zener-5.6 1 1.7143528192810002e-7 0 2.0000000000000084 10 1
    z 416 208 416 128 2 zener-5.6
    f 288 208 288 128 33 1.5 0.02
    r 288 256 288 304 0 10000
2022-01-02 hw: r2: use SiC437 for power supply
    Overhaul heavily. Schematic largely complete for changes, but needs
    review, PCB barely started.
2022-02-08 restore to kicad 6.0 compatibility
    updated to my footprintbranch, 6.0 and all that
2022-04-04 hubbish-r2: shrink to 100x80
    re-connect all the parts, and continue to shirk responsibilities to
    route the power supply again.
2022-04-07 r2: start really doing some power routing...
2022-04-07 parts used on r2 board
2022-06-13 "finished" rev2?
    ok, should we go and order this damn thing? try it one more time?
    M2.5, should i use m3?
2022-06-15 overhaul, push silk, complete "again"
2022-06-15 r2: push more, switch to m3 mounting, more silk
    added a chicken jumper to connect vbus and 5v...
2022-06-15 Add gerbers for 2022-06 round production order
2022-06-15 Update readme with pics and schematic link for r2
2022-06-15 update with moah benefits
2022-06-15 add r1 docs
2022-06-22 case design v1:
    ordered this in petg. wild assumptions about how to make spring clips.
    lets see how crazy this is. still gross with the cutouts not having
    corresponding tabs, but we want to test the clips and the mounting holes
    first..
2022-10-22 BOM revisions for a rev3
    Probably not going to bother even assembling rev2 pcbs. Was missing
    parts, found other things that were a little non-ideal.
    Decided to start revising towards making it assembleable by JLC, so
    using super cheap parts from their basic line where possible, and
    minimizing bom items.
2022-11-06 r3: start designing with the sic402
    of course, now that i started the design, we see that JLC has the
    original sic437 available for use, so we'll probably just toss this work
    :)
2022-11-08 rev3: overhaul nearly all parts to be from jlc pcba
    Only the inductor left. I've marked a few through hole parts as DNP, as
    I can solder them by hand, and already have the parts in stock. But
    everything else goes to JLC for assembly, with every attempt made to
    stick to only basic parts, or shared parts. Beyond that, price and
    stocking!
2022-11-12 r3: add power good led, add auto switch 5v sources
    copied from nanopi usb sections.
    still need to adjust the spacing of the leds, and decide on ordering,
    with or without eeprom permanently.
2022-11-13 r3: reset port leds to be 5mm separation
    better for 3mm light pipes.
    TODO: shouldn't we move the hub indicicator led into the same block?!
2022-11-15 r3: move hub led to same block/spacing
    also fixes up a few more traces that got missed when parts were resized
    (usb upstream side, and per port downstream power caps)
2022-11-17 r3: "last" tweaks
    move silk, cleaned some traces, added better ground shield to DS port,
    fattened the 5v distrib vias
2022-11-20 r3: fix spaces in lcsc fields
2022-11-20 r3: Add production files for what was ordered
2022-11-20 r3: save all laast edits too
2022-11-23 add more 3d models and get going on a new case
2022-11-23 latest step of rev3 board itself
2022-12-17 rev4: minor fixes and tweaks to rev3.
    Fixed the current mirror to use a proper matched pair.
    Added polarity protection to the sic437, to stop it being backpowered
    when it's off and we have vbus only. We're trying to make sure we can
    properly indicate whether we have local power or not, and it's being
    back powered by the 5V.
    upgraded the OCP limit to 14A. We have 10A rated parts, and 2A rated
2022-12-17 hack tool for generating eeprom contents
2022-12-17 Add our jlc pcba bom generator
2022-12-17 sim notes for ideal diode model
2022-12-18 i2c memory generator
    hooray memoryview!
2022-12-25 update port maps after testing.
2023-12-21 update readme as best memory serves
    What was I thinking? why didn't I update any of this at the time?!
2023-12-21 fix kicad jlc bom generator to include quantities
2023-12-21 rev3-2022-10: add fixme text on errors
2023-12-21 fix formatting of readme a bit
2023-12-21 gitignore more stuff
